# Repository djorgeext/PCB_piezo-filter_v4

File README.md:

Fourth version of a pre-conditioning circuit for an analog PCG signal based on a piezoelectric sensor.

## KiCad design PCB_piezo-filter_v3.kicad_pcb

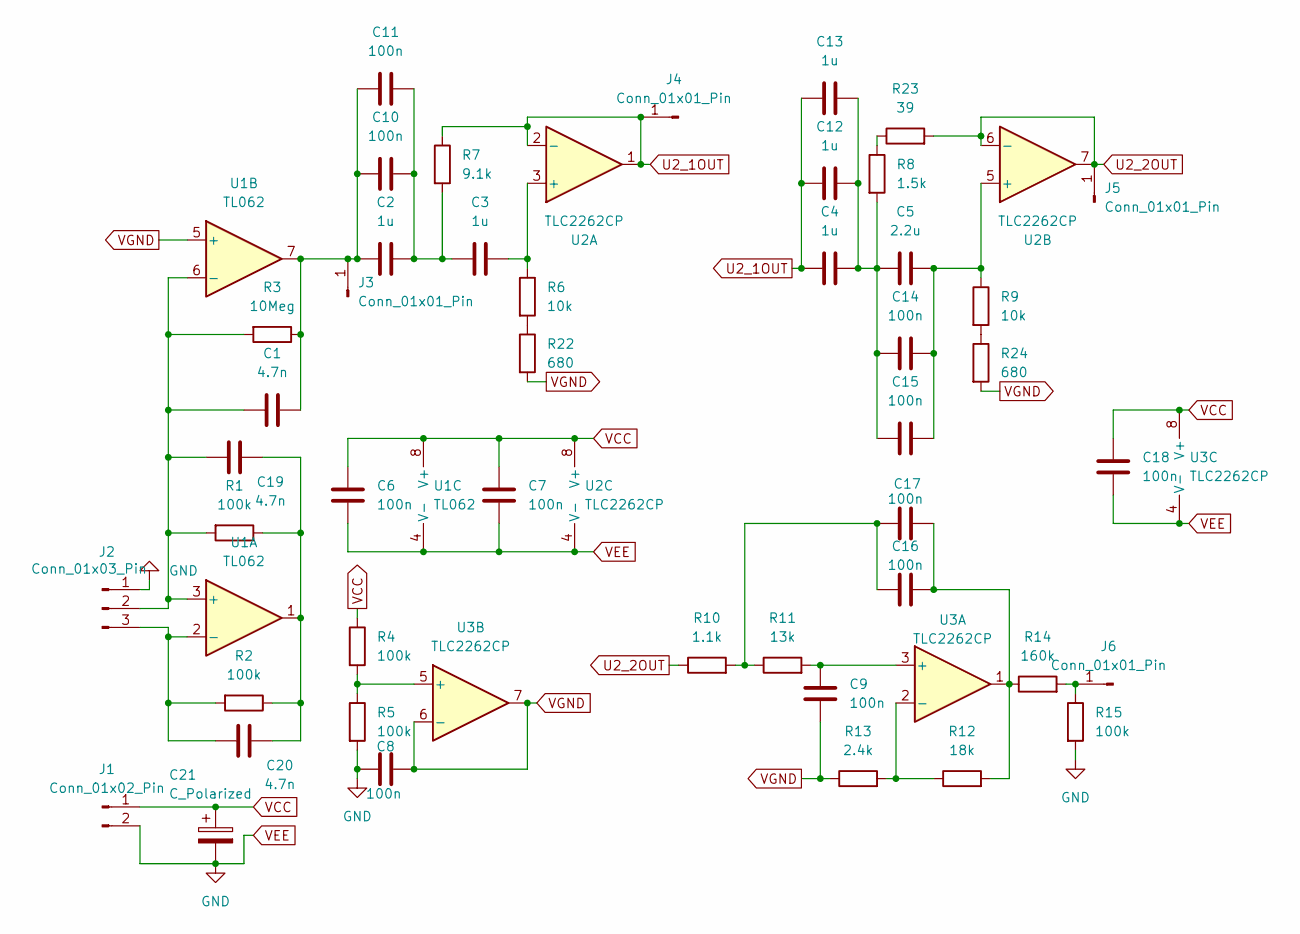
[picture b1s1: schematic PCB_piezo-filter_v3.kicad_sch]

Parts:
C1, C19, C20: 4.7n; C_Disc_D5.0mm_W2.5mm_P3.0mm
C2, C3, C4, C12, C13: 1u; C1u_p16
C5: 2.2u; C1u_p20
C6, C7, C8, C9, C10, C11, C14, C15, C16, C17, C18: 100n; C_Disc_D5.0mm_W2.5mm_P3.0mm
C21: C_Polarized; CP_Radial_D6.3mm_P2.50mm
J1: Conn_01x02_Pin; PinHeader_1x02_P2.54mm_Vertical
J2: Conn_01x03_Pin; PinHeader_1x03_P2.54mm_Vertical
J3, J4, J5, J6: Conn_01x01_Pin; PinHeader_1x01_P2.54mm_Vertical
R1, R2, R4, R5, R15: 100k; R_Axial_DIN0207_L6.3mm_D2.5mm_P7.62mm_Horizontal
R3: 10Meg; R_Axial_DIN0207_L6.3mm_D2.5mm_P7.62mm_Horizontal
R6, R9: 10k; R_Axial_DIN0207_L6.3mm_D2.5mm_P7.62mm_Horizontal
R7: 9.1k; R_Axial_DIN0207_L6.3mm_D2.5mm_P7.62mm_Horizontal
R8: 1.5k; R_Axial_DIN0207_L6.3mm_D2.5mm_P7.62mm_Horizontal
R10: 1.1k; R_Axial_DIN0207_L6.3mm_D2.5mm_P7.62mm_Horizontal
R11: 13k; R_Axial_DIN0207_L6.3mm_D2.5mm_P7.62mm_Horizontal
R12: 18k; R_Axial_DIN0207_L6.3mm_D2.5mm_P7.62mm_Horizontal
R13: 2.4k; R_Axial_DIN0207_L6.3mm_D2.5mm_P7.62mm_Horizontal
R14: 160k; R_Axial_DIN0207_L6.3mm_D2.5mm_P7.62mm_Horizontal
R22, R24: 680; R_Axial_DIN0207_L6.3mm_D2.5mm_P7.62mm_Horizontal
R23: 39; R_Axial_DIN0207_L6.3mm_D2.5mm_P7.62mm_Horizontal
U1: TL062; P8
U2, U3: TLC2262CP; P8

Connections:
unnamed: C2.2, C3.1, C10.2, C11.2, R7.2
unnamed: C4.2, C5.1, C12.2, C13.2, C14.1, C15.1, R8.2
unnamed: C16.1, C17.1, R12.2, R14.1, U3.1
unnamed: C16.2, C17.2, R10.2, R11.1
unnamed: C19.1, C20.1, R1.1, R2.1, U1.1
unnamed: C1.1, C19.2, J2.2, R1.2, R3.2, U1.3 (+), U1.6 (-)
unnamed: C20.2, J2.3, R2.2, U1.2 (-)
unnamed: C1.2, C2.1, C10.1, C11.1, J3.1, R3.1, U1.7
unnamed: J6.1, R14.2, R15.1
unnamed: R6.2, R22.1
unnamed: R8.1, R23.1
unnamed: R9.2, R24.1
unnamed: C3.2, R6.1, U2.3 (+)
unnamed: C5.2, C14.2, C15.2, R9.1, U2.5 (+)
unnamed: C9.2, R11.2, U3.3 (+)
unnamed: R12.1, R13.2, U3.2 (-)
unnamed: R4.2, R5.1, U3.5 (+)
U2_1OUT: C4.1, C12.1, C13.1, J4.1, R7.1, U2.1, U2.2 (-)
U2_2OUT: J5.1, R10.1, R23.2, U2.6 (-), U2.7
VCC: C6.2, C7.2, C18.2, C21.1, J1.1, R4.1, U1.8 (V+), U2.8 (V+), U3.8 (V+)
VEE: C6.1, C7.1, C8.1, C18.1, C21.2, J1.2, J2.1, R5.2, R15.2, U1.4 (V-), U2.4 (V-), U3.4 (V-)
VGND: C8.2, C9.1, R13.1, R22.2, R24.2, U1.5 (+), U3.6 (-), U3.7

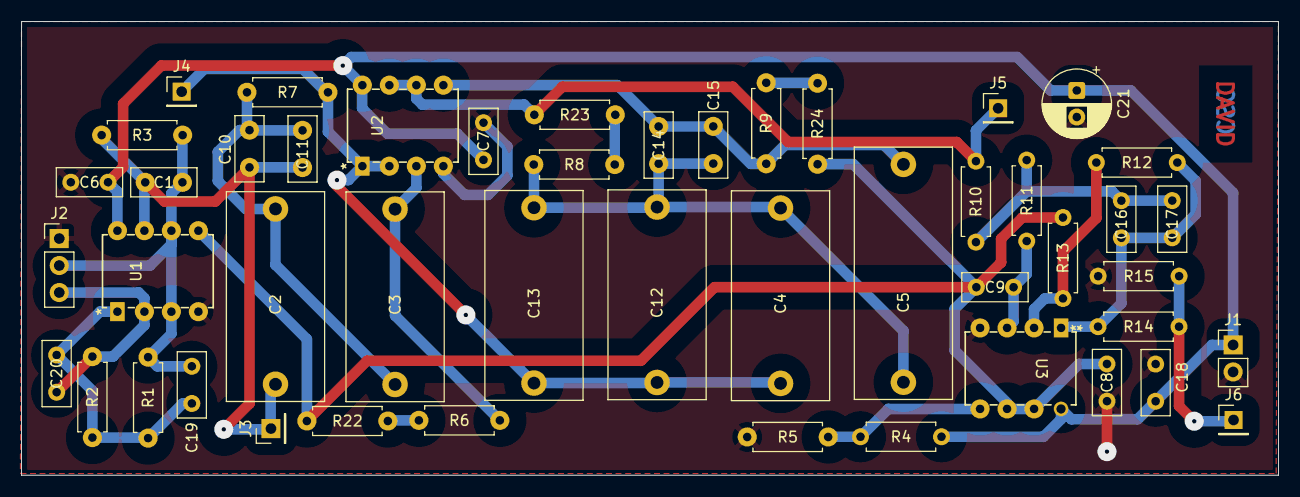
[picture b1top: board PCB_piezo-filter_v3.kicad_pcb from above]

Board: 2 copper layers, 118.3 x 42.7 mm, 48 parts (0 on the bottom side), 22 nets.
